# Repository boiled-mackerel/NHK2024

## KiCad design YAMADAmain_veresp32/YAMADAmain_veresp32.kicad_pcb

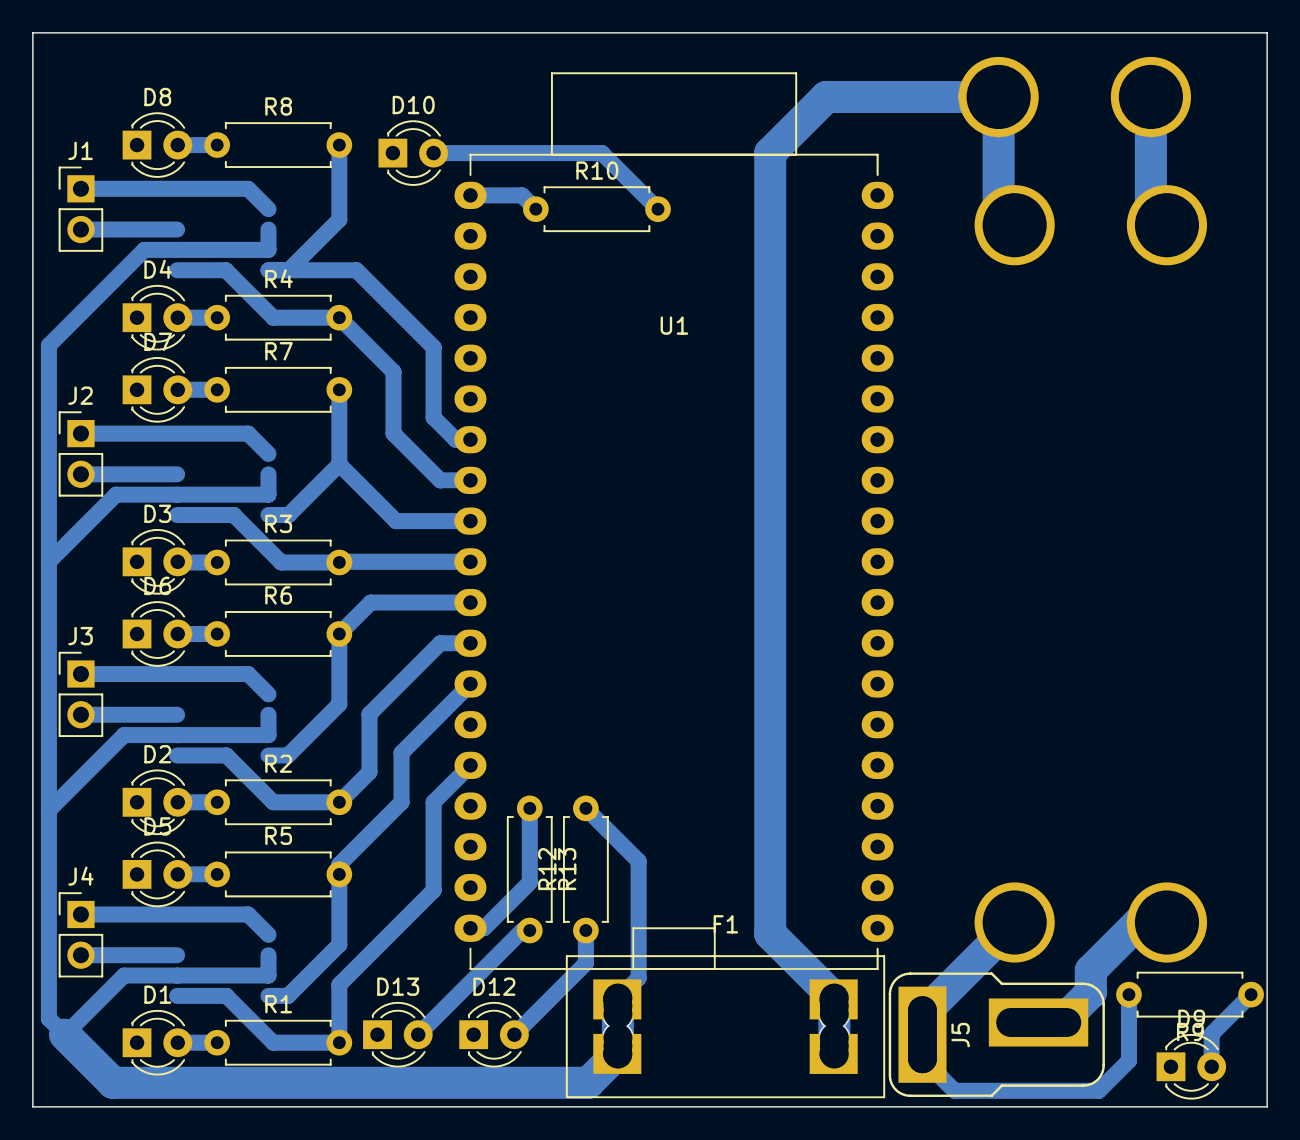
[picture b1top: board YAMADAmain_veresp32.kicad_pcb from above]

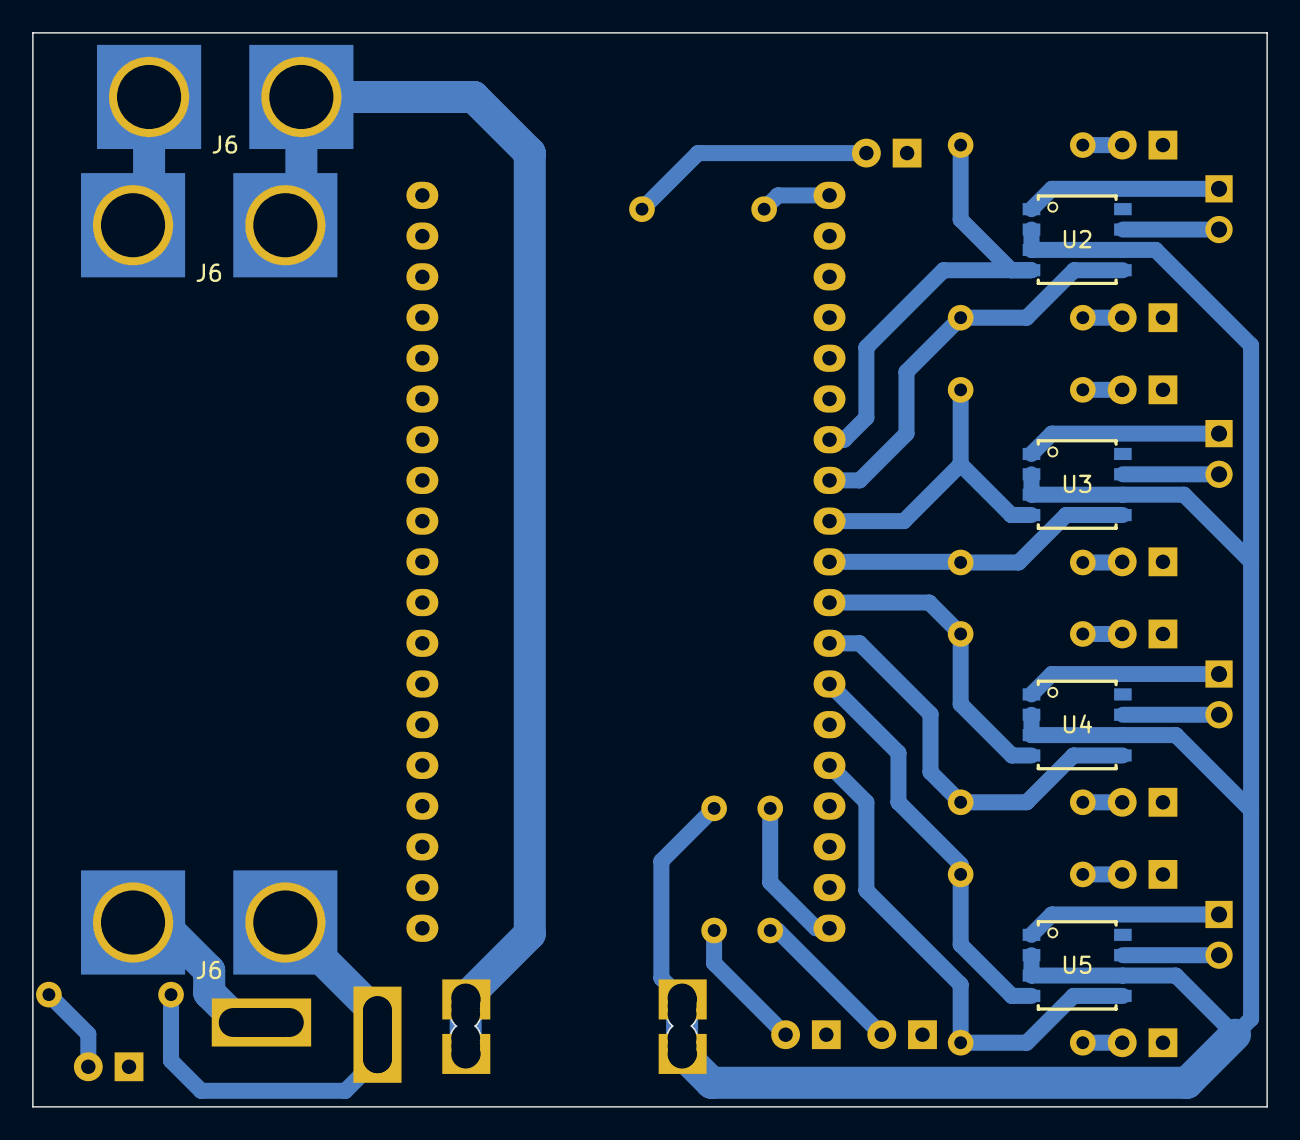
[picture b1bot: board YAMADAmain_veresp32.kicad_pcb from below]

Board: 2 copper layers, 77.0 x 67.0 mm, 38 parts (7 on the bottom side), 35 nets.

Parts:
D1: M4F; LED_D3.0mm
D2: M3F; LED_D3.0mm
D3: M2F; LED_D3.0mm
D4: M1F; LED_D3.0mm
D5: M4R; LED_D3.0mm
D6: M3R; LED_D3.0mm
D7: M2R; LED_D3.0mm
D8: M1R; LED_D3.0mm
D9: Batt; LED_D3.0mm
D10: 3.3V; LED_D3.0mm
D12: fuse; LED_D3.0mm
D13: 5V; LED_D3.0mm
F1: Fuse; FuseHolder_Carfuse
J1: M1; PinHeader_1x02_P2.54mm_Vertical
J2: M2; PinHeader_1x02_P2.54mm_Vertical
J3: M3; PinHeader_1x02_P2.54mm_Vertical
J4: M4; PinHeader_1x02_P2.54mm_Vertical
J5: Lipo_IN; Deans_Female
J6, J6#2, J6#3: power_IN; POWER_PAD_vertical
R1, R2, R3, R4, R5, R6, R7, R8, R10, R13: 1.5k; R_Axial_DIN0207_L6.3mm_D2.5mm_P7.62mm_Horizontal
R9, R12: 20k; R_Axial_DIN0207_L6.3mm_D2.5mm_P7.62mm_Horizontal
U1: ESP32-DevKitC-32E
U2, U3, U4, U5: SOP8

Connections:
+BATT: J5.1, J6#2.1, R9.2
GND: D1.1 (K), D2.1 (K), D3.1 (K), D4.1 (K), D5.1 (K), D6.1 (K), D7.1 (K), D8.1 (K), D9.1 (K), D10.1 (K), D12.1 (K), D13.1 (K), J6.2, J6#3.2, U1.14 (GND), U1.32 (GND), U1.38 (GND), U2.8 (GND), U3.8 (GND), U4.8 (GND), U5.8 (GND)
GNDPWR: J5.2, J6#2.2
unnamed: D1.2 (A), R1.1
unnamed: D2.2 (A), R2.1
unnamed: D3.2 (A), R3.1
unnamed: D4.2 (A), R4.1
unnamed: D5.2 (A), R5.1
unnamed: D6.2 (A), R6.1
unnamed: D7.2 (A), R7.1
unnamed: D8.2 (A), R8.1
unnamed: D9.2 (A), R9.1
unnamed: D10.2 (A), R10.2
unnamed: D12.2 (A), R12.1
unnamed: D13.2 (A), R13.2
unnamed: J1.1, U2.1 (OUT1)
unnamed: J1.2, U2.7 (OUT2)
unnamed: J2.1, U3.1 (OUT1)
unnamed: J2.2, U3.7 (OUT2)
unnamed: J3.1, U4.1 (OUT1)
unnamed: J3.2, U4.7 (OUT2)
unnamed: J4.1, U5.1 (OUT1)
unnamed: J4.2, U5.7 (OUT2)
unnamed: R10.1, U1.1 (3.3V)
unnamed: R13.1, U1.19 (5V)
unnamed: R5.2, U1.13 (GPIO12/ADC_CH5/MTDI), U5.4 (FIN)
unnamed: R1.2, U1.15 (GPIO13/ADC2_CH4/MTCK), U5.5 (RIN)
unnamed: R2.2, U1.12 (GPIO14/ADC2_CH6/MTMS), U4.5 (RIN)
unnamed: R7.2, U1.9 (GPIO25/ADC1_CH8/DAC_1), U3.4 (FIN)
unnamed: R3.2, U1.10 (GPIO26/ADC2_CH9/DAC_2), U3.5 (RIN)
unnamed: R6.2, U1.11 (GPIO27/ADC2_CH7), U4.4 (FIN)
unnamed: R8.2, U1.7 (GPIO32/ADC1_CH4/XTAL_32_P), U2.4 (FIN)
unnamed: R4.2, U1.8 (GPIO33/ADC1_CH5/XTAL_32_N), U2.5 (RIN)
RV_IN: F1.2, J6.1, J6#3.1
fuse_OUT: F1.1, R12.2, U2.2 (VCC), U2.3 (VCC), U2.6 (VREF), U3.2 (VCC), U3.3 (VCC), U3.6 (VREF), U4.2 (VCC), U4.3 (VCC), U4.6 (VREF), U5.2 (VCC), U5.3 (VCC), U5.6 (VREF)

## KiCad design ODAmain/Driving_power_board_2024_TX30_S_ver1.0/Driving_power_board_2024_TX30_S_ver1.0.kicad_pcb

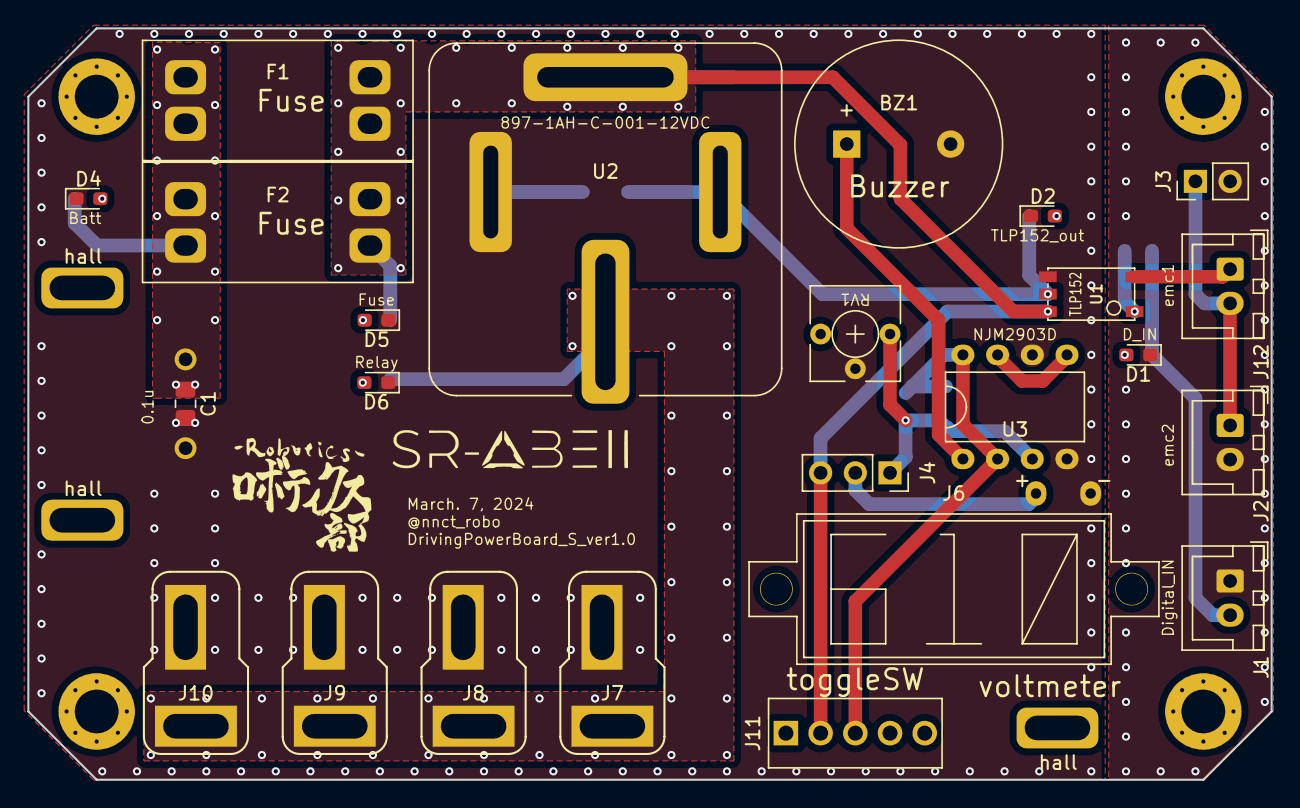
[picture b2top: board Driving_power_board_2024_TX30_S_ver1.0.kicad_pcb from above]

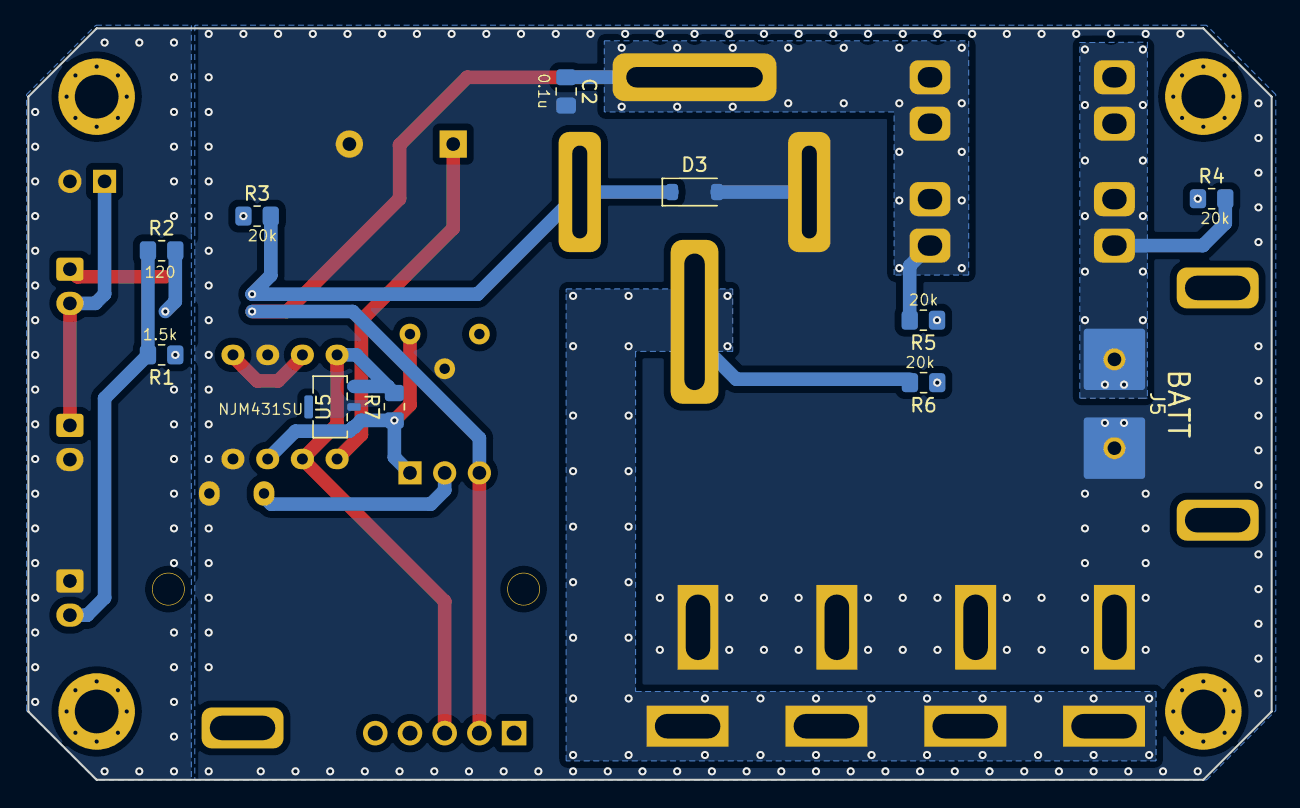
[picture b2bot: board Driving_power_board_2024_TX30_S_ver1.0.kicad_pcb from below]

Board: 2 copper layers, 91.0 x 55.0 mm, 38 parts (11 on the bottom side), 20 nets.

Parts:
BZ1: Buzzer; Buzzer_15x7.5RM7.6
C1, C2: 0.1u; C_0805_2012Metric_Pad1.18x1.45mm_HandSolder
D1: D_IN_LED; LED_0603_1608Metric_Pad1.05x0.95mm_HandSolder
D2: TLP_LED; LED_0603_1608Metric_Pad1.05x0.95mm_HandSolder
D3: D_Small; D_SOD-123
D4: Batt_LED; LED_0603_1608Metric_Pad1.05x0.95mm_HandSolder
D5: Fuse_LED; LED_0603_1608Metric_Pad1.05x0.95mm_HandSolder
D6: Relay_LED; LED_0603_1608Metric_Pad1.05x0.95mm_HandSolder
F1, F2: Fuse; FuseHolder_Carfuse
J1: control_IN; JST_XH_B2B-XH-A_1x02_P2.50mm_Vertical
J2: emc-sw_2; JST_XH_B2B-XH-A_1x02_P2.50mm_Vertical
J3: pin; PinHeader_1x02_P2.54mm_Vertical
J4: pin; PinSocket_1x03_P2.54mm_Vertical
J5: BATT; POWER_PAD
J6: voltmeter; VoltMater
J7, J8, J9, J10: deans; Deans_Female
J11: toggleSW; toggle_sw
J12: emc-sw_1; JST_XH_B2B-XH-A_1x02_P2.50mm_Vertical
R1: 1.5k; R_0805_2012Metric_Pad1.20x1.40mm_HandSolder
R2: 120; R_0805_2012Metric_Pad1.20x1.40mm_HandSolder
R3, R4, R5, R6, R7: 20k; R_0805_2012Metric_Pad1.20x1.40mm_HandSolder
RV1: R_Potentiometer; Potentiometer_3362p
U1: TLP152
U2: 897-1AH-C-001-12VDC
U3: NJM2903D; SN75176BP
U5: NJM431SU
hall: hall
hall#2, hall#3: hall

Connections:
+BATT: C1.1, F1.1, F2.1, J5.1, R4.2
Digital_IN: J1.2, R1.2, R2.1
Fuse_in: J11.3, R7.2, U3.2 (-), U3.8 (V+), U5.3 (CATHODE)
Fuse_out: C2.1, F1.2, F2.2, J4.3, J11.2, R5.2, U1.6, U2.87
GND: D1.1 (K), J1.1, J2.2, J3.2
GNDPWR: BZ1.2 (+), C1.2, C2.2, D2.1 (K), D3.2 (A), D4.1 (K), D5.1 (K), D6.1 (K), J5.2, J6.3, J7.2, J8.2, J9.2, J10.2, RV1.2, U1.4, U2.86, U3.4 (V-), U3.6 (-), U5.2 (ANODE)
unnamed: BZ1.1 (-), U3.1
unnamed: D1.2 (A), R1.1
unnamed: D2.2 (A), R3.1
unnamed: D4.2 (A), R4.1
unnamed: D5.2 (A), R5.1
unnamed: D6.2 (A), R6.1
unnamed: J4.2, J6.2
unnamed: J12.1, U1.3
unnamed: J2.1, J3.1, J12.2
unnamed: R2.2, U1.1
unnamed: U3.5 (+), U3.7
Relay_out: J7.1, J8.1, J9.1, J10.1, R6.2, U2.30
TLP152_out: D3.1 (K), R3.2, U1.5, U2.85
VEA_IN: J4.1, R7.1, RV1.1, U3.3 (+), U5.1 (REFERENCE)

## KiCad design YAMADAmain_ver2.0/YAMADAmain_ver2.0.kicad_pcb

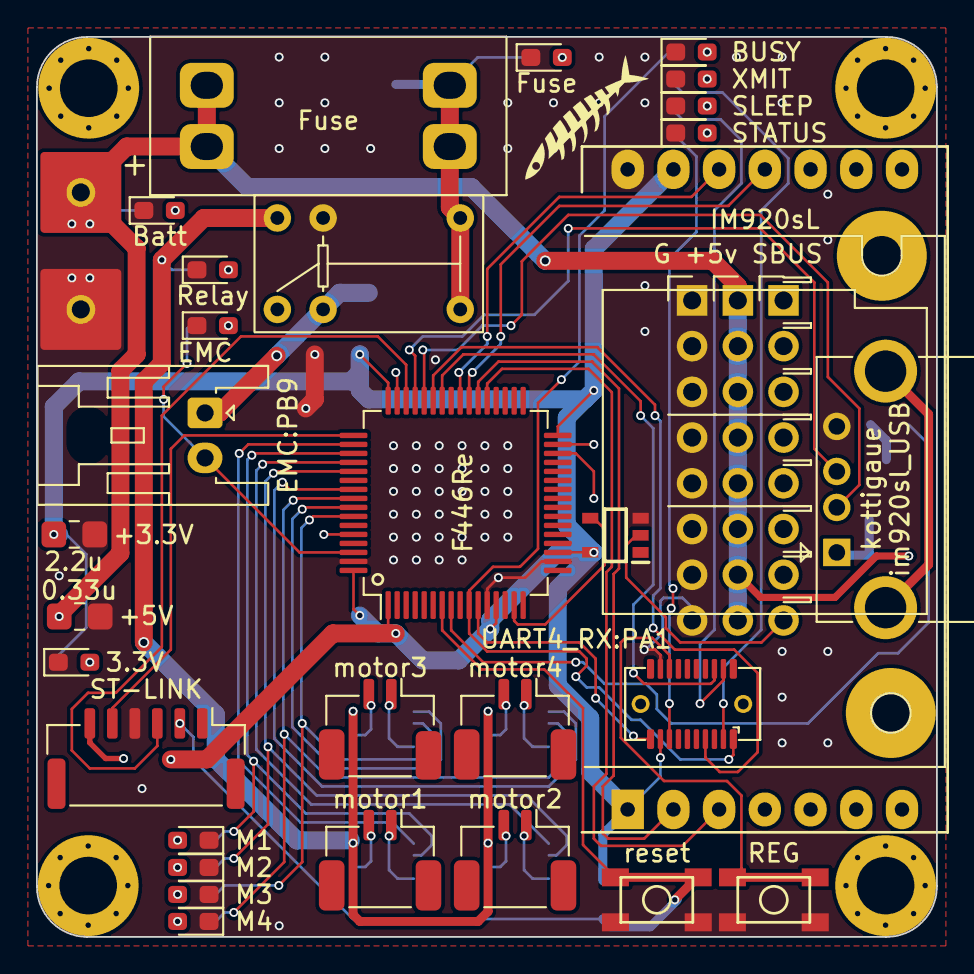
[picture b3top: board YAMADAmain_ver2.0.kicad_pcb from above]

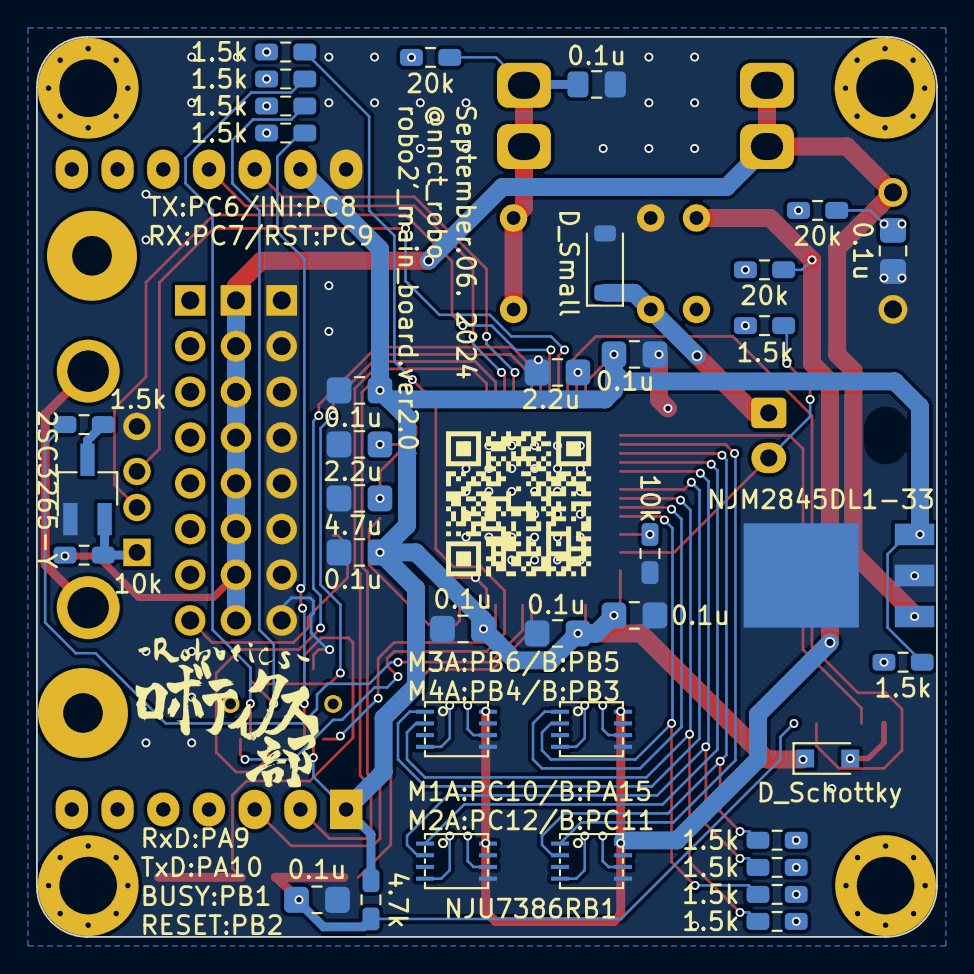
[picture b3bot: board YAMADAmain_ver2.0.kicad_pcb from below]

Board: 2 copper layers, 50.0 x 50.0 mm, 69 parts (37 on the bottom side), 63 nets.

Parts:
B_C1: 0.1u; C_0805_2012
C1: 0.33u; C_0805_2012
C2, C3, C4: 2.2u; C_0805_2012
D1: 3.3V; LED_0603_1608Metric_Pad1.05x0.95mm_HandSolder
D2: Batt; LED_0603_1608Metric_Pad1.05x0.95mm_HandSolder
D3: BUSY; LED_0603_1608Metric_Pad1.05x0.95mm_HandSolder
D4: XMIT; LED_0603_1608Metric_Pad1.05x0.95mm_HandSolder
D5: SLEEP; LED_0603_1608Metric_Pad1.05x0.95mm_HandSolder
D6: STATUS; LED_0603_1608Metric_Pad1.05x0.95mm_HandSolder
D7: Fuse; LED_0603_1608Metric_Pad1.05x0.95mm_HandSolder
D8: EMC; LED_0603_1608Metric_Pad1.05x0.95mm_HandSolder
D9: D_Small; D_SOD-123
D10: Relay; LED_0603_1608Metric_Pad1.05x0.95mm_HandSolder
D11: M4; LED_0603_1608Metric_Pad1.05x0.95mm_HandSolder
D12: M3; LED_0603_1608Metric_Pad1.05x0.95mm_HandSolder
D13: M2; LED_0603_1608Metric_Pad1.05x0.95mm_HandSolder
D14: M1; LED_0603_1608Metric_Pad1.05x0.95mm_HandSolder
F1: Fuse; FuseHolder_Carfuse
F_C1: 0.1u; C_0805_2012Metric_Pad1.18x1.45mm_HandSolder
IC1: BD7LS04G-CTL; SOT95P280X125-5N
J1: im920sl_USB; USB_A_CONNFLY_DS1095-WNR0
J2: BATT; POWER_PAD
J3: EMC:PB9; JST_XA_S02B-XASK-1_1x02_P2.50mm_Horizontal
J4: motor1; JST_GH_BM02B-GHS-TBT_1x02-1MP_P1.25mm_Vertical
J5: motor2; JST_GH_BM02B-GHS-TBT_1x02-1MP_P1.25mm_Vertical
J6: motor3; JST_GH_BM02B-GHS-TBT_1x02-1MP_P1.25mm_Vertical
J7: motor4; JST_GH_BM02B-GHS-TBT_1x02-1MP_P1.25mm_Vertical
Q1: 2SC3265-Y; 2sc3265_SC-59_Handsoldering
R1, R2, R5, R6, R7, R8, R10, R12, R13, R14, R15: 1.5k; R_0603_1608
R3, R16: 10k; R_0603_1608
R4, R9, R11: 20k; R_0603_1608
U1: NJM2845DL1-33
U2: IM920sL
U3: FEP-02; FEP-02_PIN_SOCKET
U4: REG; tact_sw_smd_skrpabe10
U5: R3006SB
U6: Y14H-1C-3DS
U7, U8, U9, U10: NJU7386RB1; NJU7386
U11: 4.7k; R_0603_1608
U12: reset; tact_sw_smd_skrpabe10
U13, U14, U19, U20, U21, U22, U23: 0.1u; C_0805_2012
U15: D_Schottky; smd_diode_SOD-323_HandSoldering_cus10f30
U16: 4.7u; C_0805_2012
U17: ST-LINK; JST_GH_BM06B-GHS-TBT_1x06-1MP_P1.25mm_Vertical
U18: STM32F446RETx-stm32; LQFP-64_10x10mm_P0.5mm

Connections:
+3.3V: C2.1, IC1.5 (VCC), R1.2, U1.3 (Vout), U2.17 (VCC), U3.1 (VCC(2.5v-5.5v)), U3.13 (PowerOn), U11.1, U14.1, U15.1 (K), U18.1 (VBAT), U18.13 (VDDA), U18.19 (VDD), U18.32 (VDD), U18.48 (VDD), U18.64 (VDD), U19.1, U20.1, U21.1, U22.1, U23.1
BAT: B_C1.1, C1.1, F1.1, J2.1, R3.2, R4.2, U1.1 (Vin), U5.2 (5V)
BOOT0: R16.1, U18.60 (BOOT0)
EMC_IN: J3.2, R10.2, U18.62 (CAN1_TX/DAC_EXTI9/DCMI_D7/I2C1_SDA/I2S2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)
FEP_INI: U3.11 (/INI), U18.39 (PC8/DCMI_D2/SDIO_D0/SYS_TRACED0/TIM3_CH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)
FEP_RST: U3.12 (/RST), U18.40 (PC9/DAC_EXTI9/DCMI_D3/I2C3_SDA/I2S_CKIN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)
Fuse_out: F1.2, F_C1.1, R9.1, U6.3, U6.6
GND: B_C1.2, C1.2, C2.2, C3.2, C4.2, D1.1 (K), D2.1 (K), D3.1 (K), D4.1 (K), D5.1 (K), D6.1 (K), D7.1 (K), D8.1 (K), D9.2 (A), D10.1 (K), D11.1 (K), D12.1 (K), D13.1 (K), D14.1 (K), F_C1.2, IC1.3 (GND), J1.4 (GND), J2.2, Q1.1 (E), R16.2, U1.2 (GND), U2.18 (GND), U3.14 (GND), U4.2, U4.4, U5.1 (GND), U6.5, U7.5 (GND), U8.5 (GND), U9.5 (GND), U10.5 (GND), U12.2, U12.4, U13.1, U14.2, U16.2, U17.4, U18.12 (VSSA), U18.18 (VSS), U18.63 (VSS), U19.2, U20.2, U21.2, U22.2, U23.2
M1FIN: R15.2, U7.2 (INA), U18.51 (PC10/DCMI_D8/I2S3_CK/QUADSPI_BK1_IO1/SD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)
M1RIN: U7.1 (INB), U18.50 (ADC1_EXTI15/ADC2_EXTI15/ADC3_EXTI15/CEC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)
M2FIN: R14.2, U8.2 (INA), U18.53 (PC12/DCMI_D9/I2C2_SDA/I2S3_SD/SDIO_CK/S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)
M2RIN: U8.1 (INB), U18.52 (PC11/ADC1_EXTI11/ADC2_EXTI11/ADC3_EXTI1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)
M3FIN: R13.2, U9.2 (INA), U18.58 (CAN2_TX/CEC/DCMI_D5/I2C1_SCL/QUADSPI_BK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)
M3RIN: U9.1 (INB), U18.57 (CAN2_RX/DCMI_D10/I2C1_SMBA/I2S1_SD/I2S3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)
M4FIN: R12.2, U10.2 (INA), U18.56 (I2C3_SDA/I2S2_WS/SPI1_MISO/SPI2_NSS/SPI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)
M4RIN: U10.1 (INB), U18.55 (I2C2_SDA/I2S1_CK/I2S3_CK/SPI1_SCK/SPI3_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)
unnamed: C3.1, U18.31 (VSS)
unnamed: C4.1, U18.47 (VSS)
unnamed: D1.2 (A), R1.1
unnamed: D2.2 (A), R4.1
unnamed: D3.2 (A), R5.2
unnamed: D4.2 (A), R6.2
unnamed: D5.2 (A), R7.2
unnamed: D6.2 (A), R8.2
unnamed: D7.2 (A), R9.2
unnamed: D8.2 (A), R10.1
unnamed: D9.1 (K), J3.1, U6.2
unnamed: D10.2 (A), R11.1
unnamed: D11.2 (A), R12.1
unnamed: D12.2 (A), R13.1
unnamed: D13.2 (A), R14.1
unnamed: D14.2 (A), R15.1
unnamed: J1.1 (VBUS), Q1.2 (C), R3.1
unnamed: Q1.3 (B), R2.2
unnamed: R6.1, U2.3 (IO3/XMIT)
unnamed: R7.1, U2.4 (IO4/SLEEP)
unnamed: U2.16 (REG), U4.1, U4.3
unnamed: R8.1, U2.15 (SATUS)
unnamed: U15.2 (A), U17.6
unnamed: U16.1, U18.30 (VCAP_1)
PC_6_Serial6TX: U3.3 (TXD(DataIn)), U18.37 (PC6/DCMI_D0/FMPI2C1_SCL/I2S2_MCK/SDIO_D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)
PC_7_Serial6RX: U3.2 (RXD(DateOut)), U18.38 (PC7/DCMI_D1/FMPI2C1_SDA/I2S2_CK/I2S3_MC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)
RST: U11.2, U12.1, U12.3, U13.2, U17.2, U18.7 (NRST)
Relay_out: R11.2, U6.4, U7.8 (VDD), U8.8 (VDD), U9.8 (VDD), U10.8 (VDD)
SBUS: IC1.2 (A), U5.10 (S.BUS)
SWCLK: U17.5, U18.49 (SYS_JTCK-SWCLK/PA14)
SWDIO: U17.3, U18.46 (SYS_JTMS-SWDIO/PA13)
UART4_RX: IC1.4 (Y), U18.15 (ADC1_IN1/ADC2_IN1/ADC3_IN1/QUADSPI_BK1_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)
im920sl_BUSY: R5.1, U2.1 (BUSY), U18.10 (PC2/ADC1_IN12/ADC2_IN12/ADC3_IN12/SPI2_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)
im920sl_D+: J1.3 (D+), U18.45 (CAN1_TX/TIM1_ETR/USART1_RTS/USB_OTG_FS_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)
im920sl_D-: J1.2 (D-), U18.44 (ADC1_EXTI11/ADC2_EXTI11/ADC3_EXTI11/CAN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)
im920sl_RESET: U2.19 (RESET), U18.11 (PC3/ADC1_IN13/ADC2_IN13/ADC3_IN13/I2S2_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)
im920sl_RxD: U2.6 (RxD), U18.42 (DAC_EXTI9/DCMI_D0/I2C3_SMBA/I2S2_CK/SAI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)
im920sl_TxD: U2.7 (TxD), U18.43 (DCMI_D1/TIM1_CH3/USART1_RX/USB_OTG_FS_I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)
im920sl_zettairesetsaseruMAN: R2.1, U18.8 (PC0/ADC1_IN10/ADC2_IN10/ADC3_IN10/SAI1_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)
motor1_A: J4.1, U7.4 (OUTA)
motor1_B: J4.2, U7.6 (OUTB)
motor2_A: J5.1, U8.4 (OUTA)
motor2_B: J5.2, U8.6 (OUTB)
motor3_A: J6.1, U9.4 (OUTA)
motor3_B: J6.2, U9.6 (OUTB)
motor4_A: J7.1, U10.4 (OUTA)
motor4_B: J7.2, U10.6 (OUTB)

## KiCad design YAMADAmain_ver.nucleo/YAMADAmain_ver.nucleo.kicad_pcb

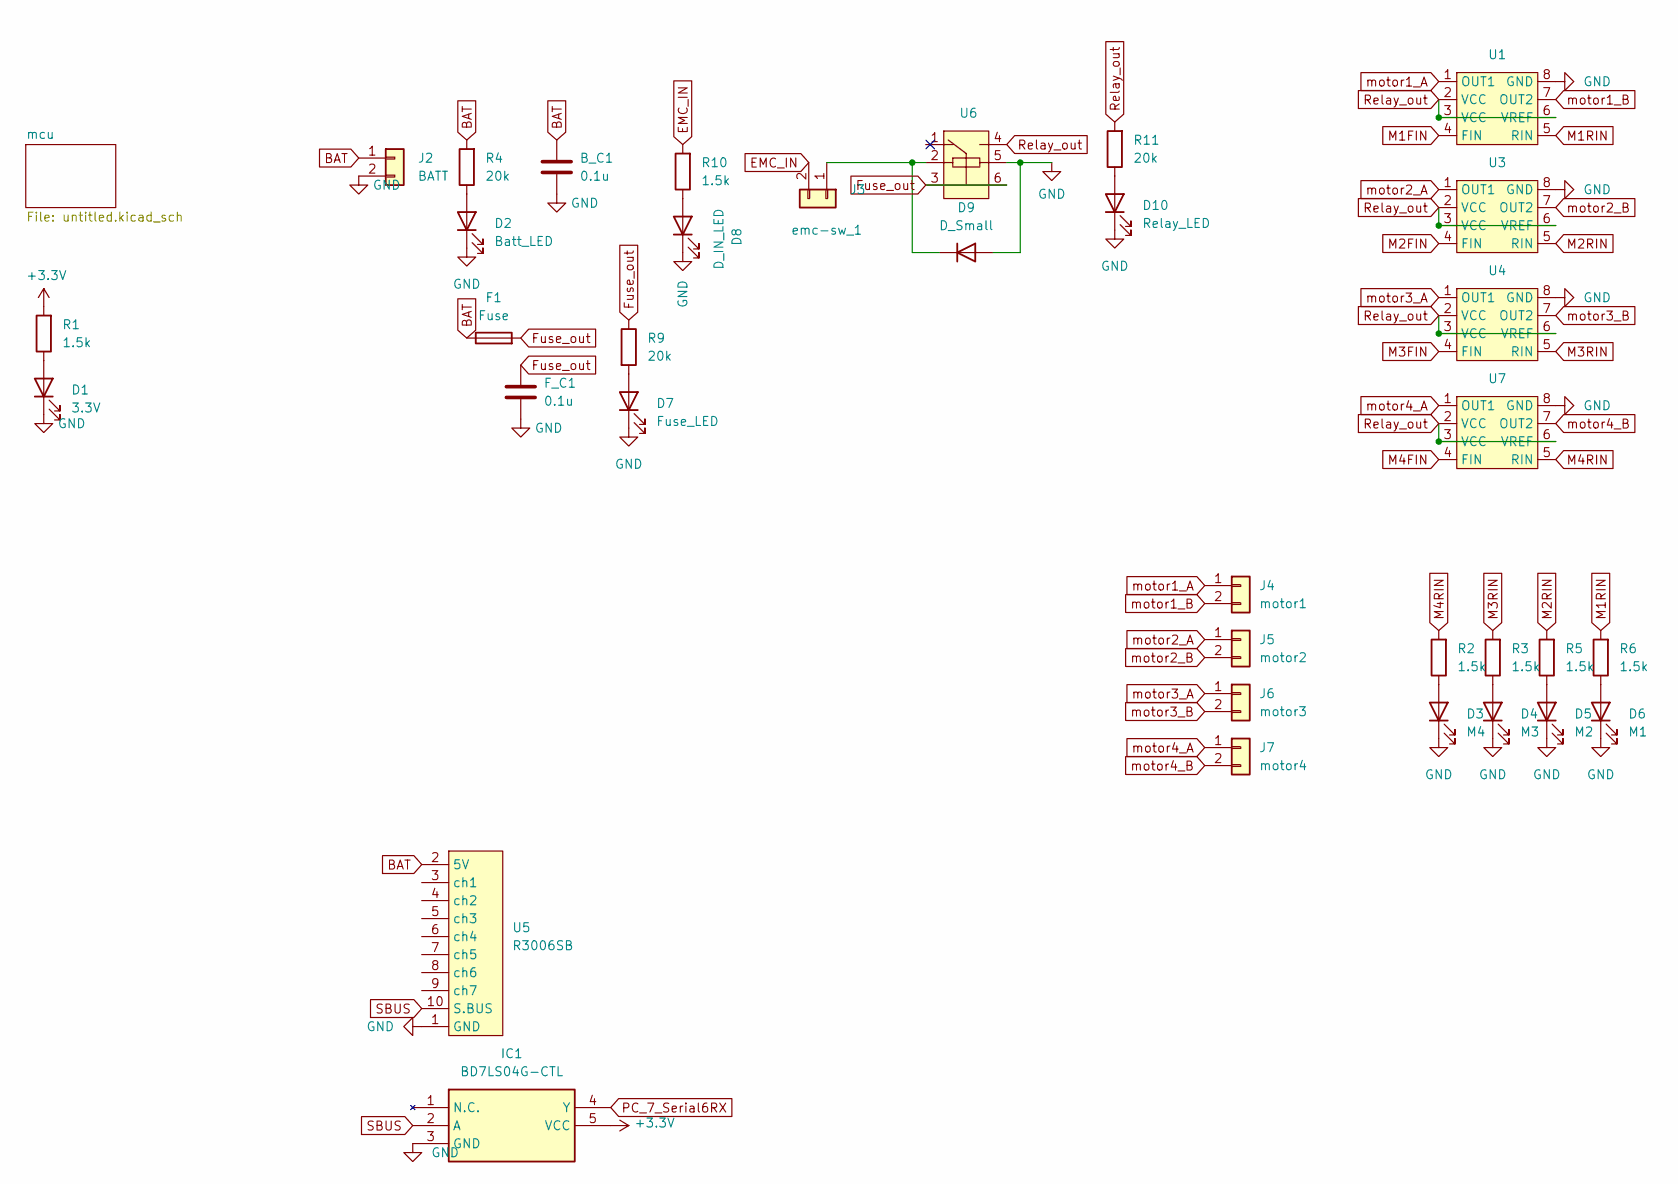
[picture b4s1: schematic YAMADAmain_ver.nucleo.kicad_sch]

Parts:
B_C1: 0.1u; C_0805_2012
D1: 3.3V; LED_D3.0mm
D2: Batt_LED; LED_D3.0mm
D3: M4; LED_D3.0mm
D4: M3; LED_D3.0mm
D5: M2; LED_D3.0mm
D6: M1; LED_D3.0mm
D7: Fuse_LED; LED_D3.0mm
D8: D_IN_LED; LED_D3.0mm
D9: D_Small; D_SOD-123
D10: Relay_LED; LED_D3.0mm
F1: Fuse; FuseHolder_Carfuse
F_C1: 0.1u; C_0805_2012Metric_Pad1.18x1.45mm_HandSolder
IC1: BD7LS04G-CTL; SOT95P280X125-5N; Manufacturer_Part_Number BD7LS04G-CTL
J2: BATT; POWER_PAD
J3: emc-sw_1; JST_XA_S02B-XASK-1_1x02_P2.50mm_Horizontal
J4: motor1; JST_GH_BM02B-GHS-TBT_1x02-1MP_P1.25mm_Vertical
J5: motor2; JST_GH_BM02B-GHS-TBT_1x02-1MP_P1.25mm_Vertical
J6: motor3; JST_GH_BM02B-GHS-TBT_1x02-1MP_P1.25mm_Vertical
J7: motor4; JST_GH_BM02B-GHS-TBT_1x02-1MP_P1.25mm_Vertical
R1, R2, R3, R5, R6, R10: 1.5k; R_Axial_DIN0207_L6.3mm_D2.5mm_P7.62mm_Horizontal
R4, R9, R11: 20k; R_Axial_DIN0207_L6.3mm_D2.5mm_P7.62mm_Horizontal
U1, U3, U4, U7: SOP8
U5: R3006SB
U6: Y14H-1C-3DS

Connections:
+3.3V: IC1.5 (VCC), R1.2; also elsewhere on the board
BAT: B_C1.1, F1.1, J2.1, R4.2, U5.2 (5V); also elsewhere on the board
EMC_IN: J3.2, R10.2; also elsewhere on the board
Fuse_out: F1.2, F_C1.1, R9.1, U6.3, U6.6
GND: B_C1.2, D1.1 (K), D2.1 (K), D3.1 (K), D4.1 (K), D5.1 (K), D6.1 (K), D7.1 (K), D8.1 (K), D9.2 (A), D10.1 (K), F_C1.2, IC1.3 (GND), J2.2, U1.8 (GND), U3.8 (GND), U4.8 (GND), U5.1 (GND), U6.5, U7.8 (GND); also elsewhere on the board
M1FIN: U1.4 (FIN); also elsewhere on the board
M1RIN: R6.2, U1.5 (RIN); also elsewhere on the board
M2FIN: U3.4 (FIN); also elsewhere on the board
M2RIN: R5.2, U3.5 (RIN); also elsewhere on the board
M3FIN: U4.4 (FIN); also elsewhere on the board
M3RIN: R3.2, U4.5 (RIN); also elsewhere on the board
M4FIN: U7.4 (FIN); also elsewhere on the board
M4RIN: R2.2, U7.5 (RIN); also elsewhere on the board
unnamed: D1.2 (A), R1.1
unnamed: D2.2 (A), R4.1
unnamed: D3.2 (A), R2.1
unnamed: D4.2 (A), R3.1
unnamed: D5.2 (A), R5.1
unnamed: D6.2 (A), R6.1
unnamed: D7.2 (A), R9.2
unnamed: D8.2 (A), R10.1
unnamed: D9.1 (K), J3.1, U6.2
unnamed: D10.2 (A), R11.1
PC_7_Serial6RX: IC1.4 (Y); also elsewhere on the board
Relay_out: R11.2, U1.2 (VCC), U1.3 (VCC), U1.6 (VREF), U3.2 (VCC), U3.3 (VCC), U3.6 (VREF), U4.2 (VCC), U4.3 (VCC), U4.6 (VREF), U6.4, U7.2 (VCC), U7.3 (VCC), U7.6 (VREF)
SBUS: IC1.2 (A), U5.10 (S.BUS)
motor1_A: J4.1, U1.1 (OUT1)
motor1_B: J4.2, U1.7 (OUT2)
motor2_A: J5.1, U3.1 (OUT1)
motor2_B: J5.2, U3.7 (OUT2)
motor3_A: J6.1, U4.1 (OUT1)
motor3_B: J6.2, U4.7 (OUT2)
motor4_A: J7.1, U7.1 (OUT1)
motor4_B: J7.2, U7.7 (OUT2)

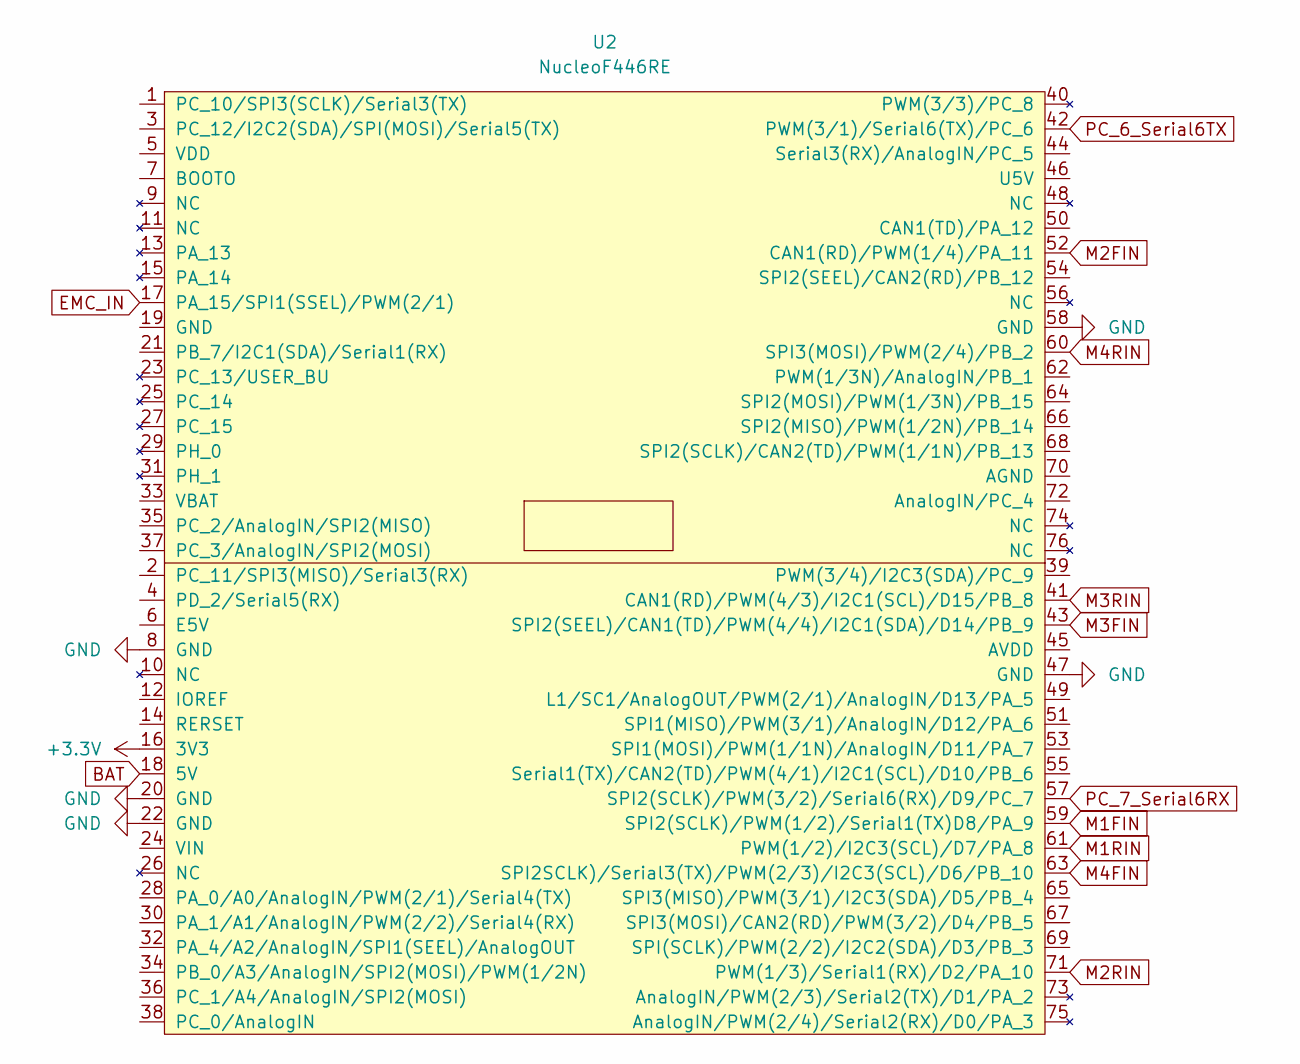
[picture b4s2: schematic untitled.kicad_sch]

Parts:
U2: NucleoF446RE; Nucleo64Board_F446RE

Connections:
+3.3V: U2.16 (3V3); also elsewhere on the board
BAT: U2.18 (5V); also elsewhere on the board
EMC_IN: U2.17 (PA_15/SPI1(SSEL)/PWM(2/1)); also elsewhere on the board
GND: U2.8 (GND), U2.20 (GND), U2.22 (GND), U2.47 (GND), U2.58 (GND); also elsewhere on the board
M1FIN: U2.59 (SPI2(SCLK)/PWM(1/2)/Serial1(TX)D8/PA_9); also elsewhere on the board
M1RIN: U2.61 (PWM(1/2)/I2C3(SCL)/D7/PA_8); also elsewhere on the board
M2FIN: U2.52 (CAN1(RD)/PWM(1/4)/PA_11); also elsewhere on the board
M2RIN: U2.71 (PWM(1/3)/Serial1(RX)/D2/PA_10); also elsewhere on the board
M3FIN: U2.43 (SPI2(SEEL)/CAN1(TD)/PWM(4/4)/I2C1(SDA)/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); also elsewhere on the board
M3RIN: U2.41 (CAN1(RD)/PWM(4/3)/I2C1(SCL)/D15/PB_8); also elsewhere on the board
M4FIN: U2.63 (SPI2SCLK)/Serial3(TX)/PWM(2/3)/I2C3(SCL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); also elsewhere on the board
M4RIN: U2.60 (SPI3(MOSI)/PWM(2/4)/PB_2); also elsewhere on the board
PC_6_Serial6TX: U2.42 (PWM(3/1)/Serial6(TX)/PC_6)
PC_7_Serial6RX: U2.57 (SPI2(SCLK)/PWM(3/2)/Serial6(RX)/D9/PC_7); also elsewhere on the board

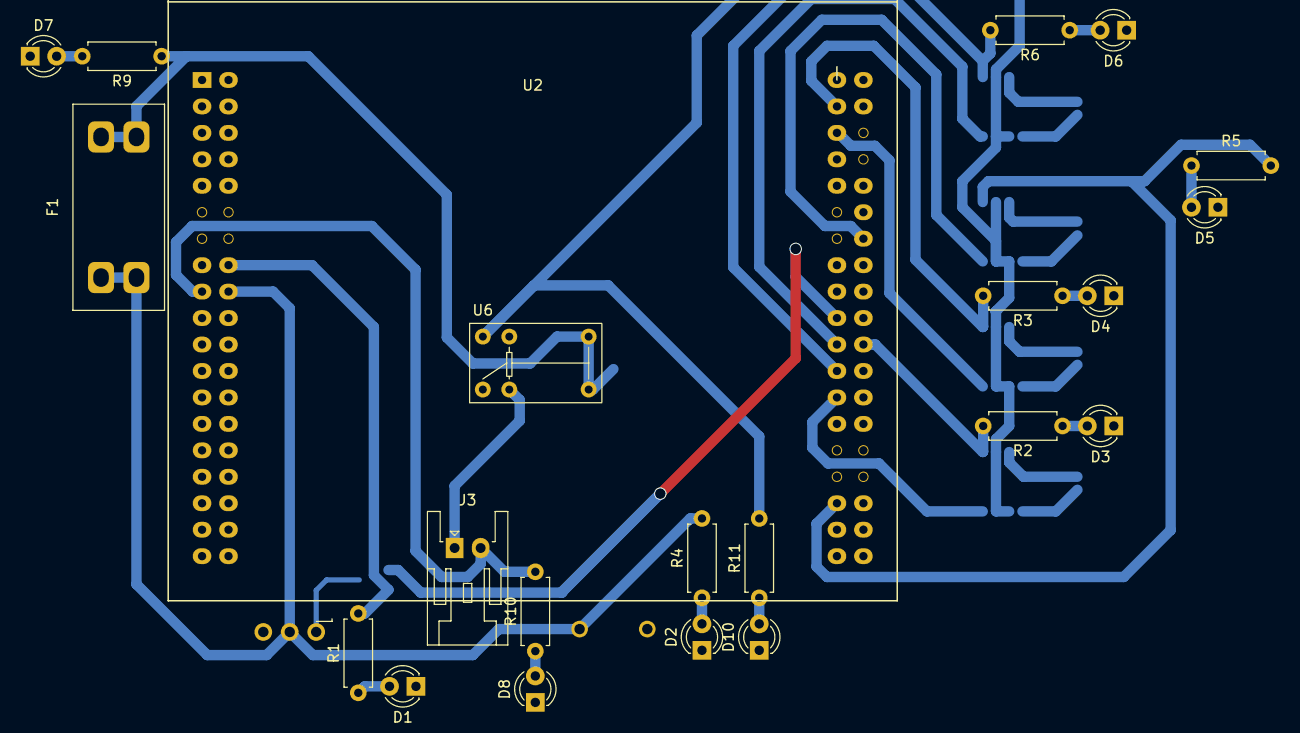
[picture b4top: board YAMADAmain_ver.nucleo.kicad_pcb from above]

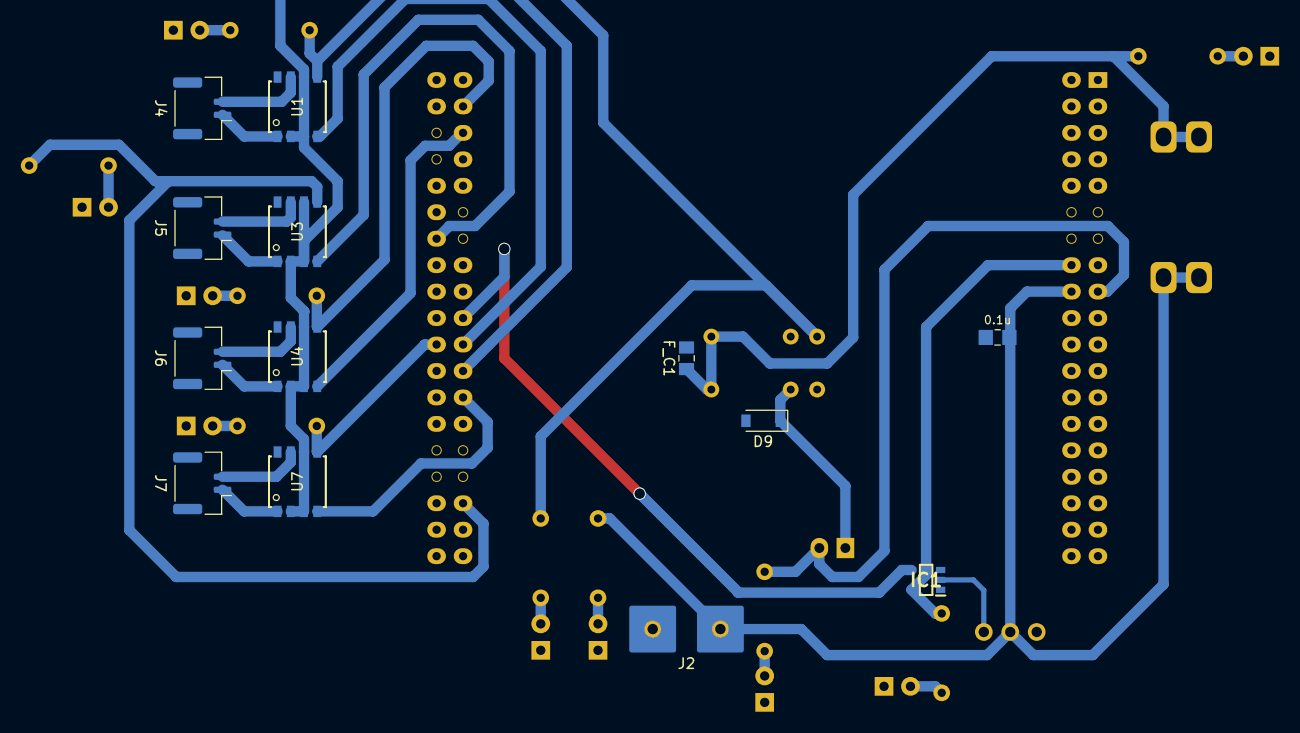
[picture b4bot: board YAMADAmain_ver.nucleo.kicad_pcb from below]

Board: 2 copper layers, 36 parts (13 on the bottom side), 34 nets.
